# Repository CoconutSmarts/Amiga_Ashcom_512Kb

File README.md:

# Amiga_Ashcom_512Kb
Reproduction of the PCB for an Ashcom 512kb memory expansion, for Amiga 500s.   This was done as a learning exercise, after finding an Ashcom board with battery damage.  Rather than bodge the damaged board, I decided to replace the board.  Of course it would have been quicker and cheaper to buy a more modern equivalent, but where's the fun in that?

## Reproduction
The KiCad files (schematic and pcb) are available here.   Note the schematic and pcb were drawn separately.  I started with the intention of just re-creating the PCB, but then decided to create the schematic for completeness.  If there are any design issues with the expansion, then the issues will persist in this reproduction.  Along the same lines, neither I have replaced the battery with a CR2032.

## KiCAD Version 
KiCAD version 9.0.3.   The schematic and PCB are contained in the schematic.   The schematic was reversed manually from the PCB, so could contain errors.   The PCB should be considered the golden source.

## Oddities
The dsign seems a somewhat more basic (and cheaper) design that the official A501 expansion.  Perhaps related to this, a few curiousities were found:-
1) Pin 5 of the memory chips are documented as Not Connected.   Yet the PCB connects these pins to GND.
2) Pin 34 and Pin 33 on the connector are shorted.   Using Raemixx500 as a reference, these pins seem to be ~CLKCS and GND.  On an Amiga 501 the signal is sent to the RTC ~CS0 input, on the Ashcom it is grounded.  Another cost saving decision?
3) The RTC clock circuit has no variable capacitor (the A501 has a fixed and variable capacitor with the crystal).
4) The holes for C9 are present on the original PCB, but not populated.  As there are no component markings, Ive assumed this was intended for a capacitor across VDD and GND (on the RTC IC), but the manufacturer obviously didnt feel this capacitor was necessary.
5) There are no decoupling capacitors across VCC and GND for U2 and U6.  Either the manufacturer didn't think decoupling capacitors were needed for U2 and U5, or it's another cost saving decision.

In summary this seems a stripped down design when compared to the A501.  Does this have any nagative implications?

## Gerbers and PCB Production
Gerber files were successfully produced by PCBWAY.   After building the board was tested in an Amiga 500 (1.3 workbench) with no issues.

Using Amiga Test Kit, the memory and RTC tested successfully:-

 -  

## BOM

| Id | Designator | Footprint | Quantity | Designation Supplier | ref |
| --- | --- | --- | --- | --- | --- |
|1|C7,C8|C_Disc_D3.0mm_W1.6mm_P2.50mm|2|22pF|
|2|BT1|Varta_2.4v_150mAh|1|2.4V 150mAh|
|3|Y9|Crystal_C26-LF_D2.1mm_L6.5mm_Vertical|1|32768Hz|
|4|C1,C3,C4,C5,C9|C_Axial_L5.1mm_D3.1mm_P7.50mm_Horizontal|5|100nF|
|5|RN1,RN3,RN2|R_Array_SIP8|3|22ohm|
|6|D1|D_A-405_P7.62mm_Horizontal|1|1N914|			
|7|U1|DIP-14_W7.62mm_LongPads|1|74LS00N|	
|8|S1|780565|1|SPDT Switch, Right Angle, 2.54mm pitch, Enable/Disable|
|9|U2,U3,U4,U5|DIP-20_W7.62mm_LongPads|4|DRAM 256Kx4-bit DIP20|
|10|J1|PinSocket_2x28_P2.54mm_Horizontal|1|Female trap door connector 2x28 2.54mm Right Angled|
|11|U6|DIP-18_W7.62mm_LongPads|1|M6242B RTC|
|12|R1|R_Axial_DIN0204_L3.6mm_D1.6mm_P7.62mm_Horizontal|1|47ohm|
|13|R2|R_Axial_DIN0204_L3.6mm_D1.6mm_P7.62mm_Horizontal|1|510ohm|

The PCB seems designed for a 2.4V or a 3.6V NiMh rechargeable battery.  R2 is sized to trickle charge a 2.4v cell at around 4mA.   R2 should be changed accordingly if a 3.6v cell is used.  By my calcs that would be around 200ohms, but I have not tested this configuration.

The RTC components can be left out, and the board will then just function as a memory expansion (C7, C8, C9, Y9, BT1, D1, R2, U6, C9 can be omitted).

## References
1) https://github.com/SukkoPera/Raemixx500 
2) https://amigawiki.org/dnl/schematics/A500_R6.pdf

## Damaged PCB Pictures
The following pictures show the original PCBs, and were used to recreate the PCB layout.

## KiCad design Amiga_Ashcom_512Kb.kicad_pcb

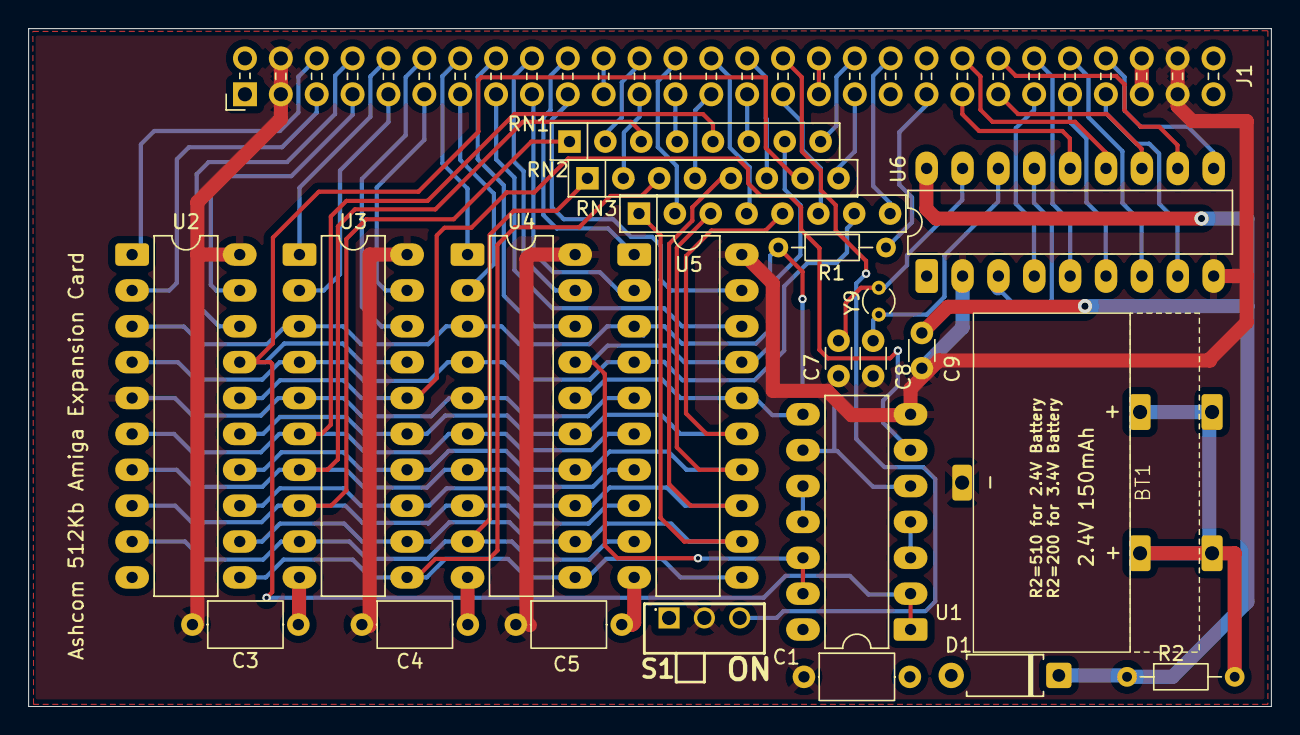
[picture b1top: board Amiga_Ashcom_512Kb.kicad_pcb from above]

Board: 2 copper layers, 88.0 x 48.0 mm, 23 parts (0 on the bottom side), 65 nets.

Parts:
BT1: 2.4V 150mAh; Varta_2.4v_150mAh
C1, C3, C4, C5: 100nF; C_Axial_L5.1mm_D3.1mm_P7.50mm_Horizontal
C7, C8: 22pF; C_Disc_D3.0mm_W1.6mm_P2.50mm
C9: 100nF; C_Disc_D3.0mm_W1.6mm_P2.50mm
D1: 1N914; D_A-405_P7.62mm_Horizontal
J1: PinSocket_2x28_P2.54mm_Horizontal
R1: 47; R_Axial_DIN0204_L3.6mm_D1.6mm_P7.62mm_Horizontal
R2: 510; R_Axial_DIN0204_L3.6mm_D1.6mm_P7.62mm_Horizontal
RN1, RN2, RN3: 22; R_Array_SIP8
S1: Enable/Disable; 780565
U1: 74LS00N; DIP-14_W7.62mm_LongPads
U2, U3, U4, U5: 256kb x 4; DIP-20_W7.62mm_LongPads
U6: M6242B; DIP-18_W7.62mm_LongPads
Y9: 32768Hz; Crystal_C26-LF_D2.1mm_L6.5mm_Vertical

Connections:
+2.4V: BT1.2, BT1.3, R2.2
A0: RN2.1, U2.9, U3.9, U4.9, U5.9
A1: RN1.1, U2.8, U3.8, U4.8, U5.8
A2: RN1.3, U2.7, U3.7, U4.7, U5.7
A3: RN3.1, U2.12, U3.12, U4.12, U5.12
A4: RN2.3, U2.11, U3.11, U4.11, U5.11
A5: RN3.3, U2.14, U3.14, U4.14, U5.14
A6: RN1.5, U2.6, U3.6, U4.6, U5.6
A7: RN2.5, U2.13, U3.13, U4.13, U5.13
A8: RN3.5, U2.15, U3.15, U4.15, U5.15
BDRA0: J1.23, RN2.2
BDRA1: J1.24, RN1.2
BDRA2: J1.25, RN1.4
BDRA3: J1.26, RN3.2
BDRA4: J1.27, RN2.4
BDRA5: J1.28, RN3.4
BDRA6: J1.29, RN1.6
BDRA7: J1.30, RN2.6
BDRA8: J1.31, RN3.6
CASL: U1.3, U1.4
CASU: U1.10, U1.11
DRD0: J1.5, U2.2
DRD1: J1.6, U2.1
DRD2: J1.7, U2.19
DRD3: J1.8, U2.18
DRD4: J1.9, U3.2
DRD5: J1.10, U3.1
DRD6: J1.11, U3.19
DRD7: J1.12, U3.18
DRD8: J1.13, U4.2
DRD9: J1.14, U4.1
DRD10: J1.15, U5.18
DRD11: J1.16, U4.18
DRD12: J1.17, U5.2
DRD13: J1.18, U4.19
DRD14: J1.19, U5.19
DRD15: J1.20, U5.1
GND: BT1.1, C1.1, C3.1, C4.1, C5.1, C7.2, C8.2, C9.2, J1.3, J1.4, J1.53, J1.54, S1.2, U1.7, U2.5, U2.20, U3.5, U3.20, U4.5, U4.20, U5.5, U5.20, U6.2, U6.9
Link_21_22: J1.21, J1.22
Link_33_34: J1.33, J1.34
VCC: C1.2, C3.2, C4.2, C5.2, D1.2, J1.1, J1.2, J1.51, J1.52, U1.14, U2.10, U3.10, U4.10, U5.10, U6.3, U6.15
VDD: C9.1, D1.1, R2.1, U6.18
XA2: J1.45, U6.4
XA3: J1.46, U6.5
XA4: J1.47, U6.6
XA5: J1.48, U6.7
XD0: J1.41, U6.14
XD1: J1.42, U6.13
XD2: J1.43, U6.12
XD3: J1.44, U6.11
XT: C8.1, U6.16, Y9.2
~BCASL1: J1.35, RN2.8
~BCASU1: J1.36, RN1.8
~BRAS0: J1.38, RN3.8
~BWE: J1.39, R1.2
~CASL: RN2.7, U1.1, U1.2, U2.17, U3.17
~CASU: RN1.7, U1.12, U1.13, U4.17, U5.17
~CLKRD: J1.49, U6.8
~CLKWR: J1.50, U6.10
~EXRAM: J1.32, S1.3
~OEL: U1.6, U2.16, U3.16
~OEU: U1.8, U4.16, U5.16
~RAS: RN3.7, U2.4, U3.4, U4.4, U5.4
~WE: R1.1, U1.5, U1.9, U2.3, U3.3, U4.3, U5.3
~XT: C7.1, U6.17, Y9.1

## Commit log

2025-07-23 Initial version of PCB and Schematic
2025-07-24 Annotated the schematic to match the PCB, and added experimental gerbers.
2025-07-24 Updated readme.
2025-08-01 Update README.md, add BOM
2025-08-02 Fix R1/R2 references and values, change C9 to 100nF
2025-08-05 Slightly increase width of board, move ON/OFF to correct layer, add additional info to silkscreen.
2025-08-05 Correct readme
2025-08-05 Add new version of gerbers.
2025-11-25 Fix typos and improve clarity in README.md
    Corrected typos and clarified descriptions in the README.
